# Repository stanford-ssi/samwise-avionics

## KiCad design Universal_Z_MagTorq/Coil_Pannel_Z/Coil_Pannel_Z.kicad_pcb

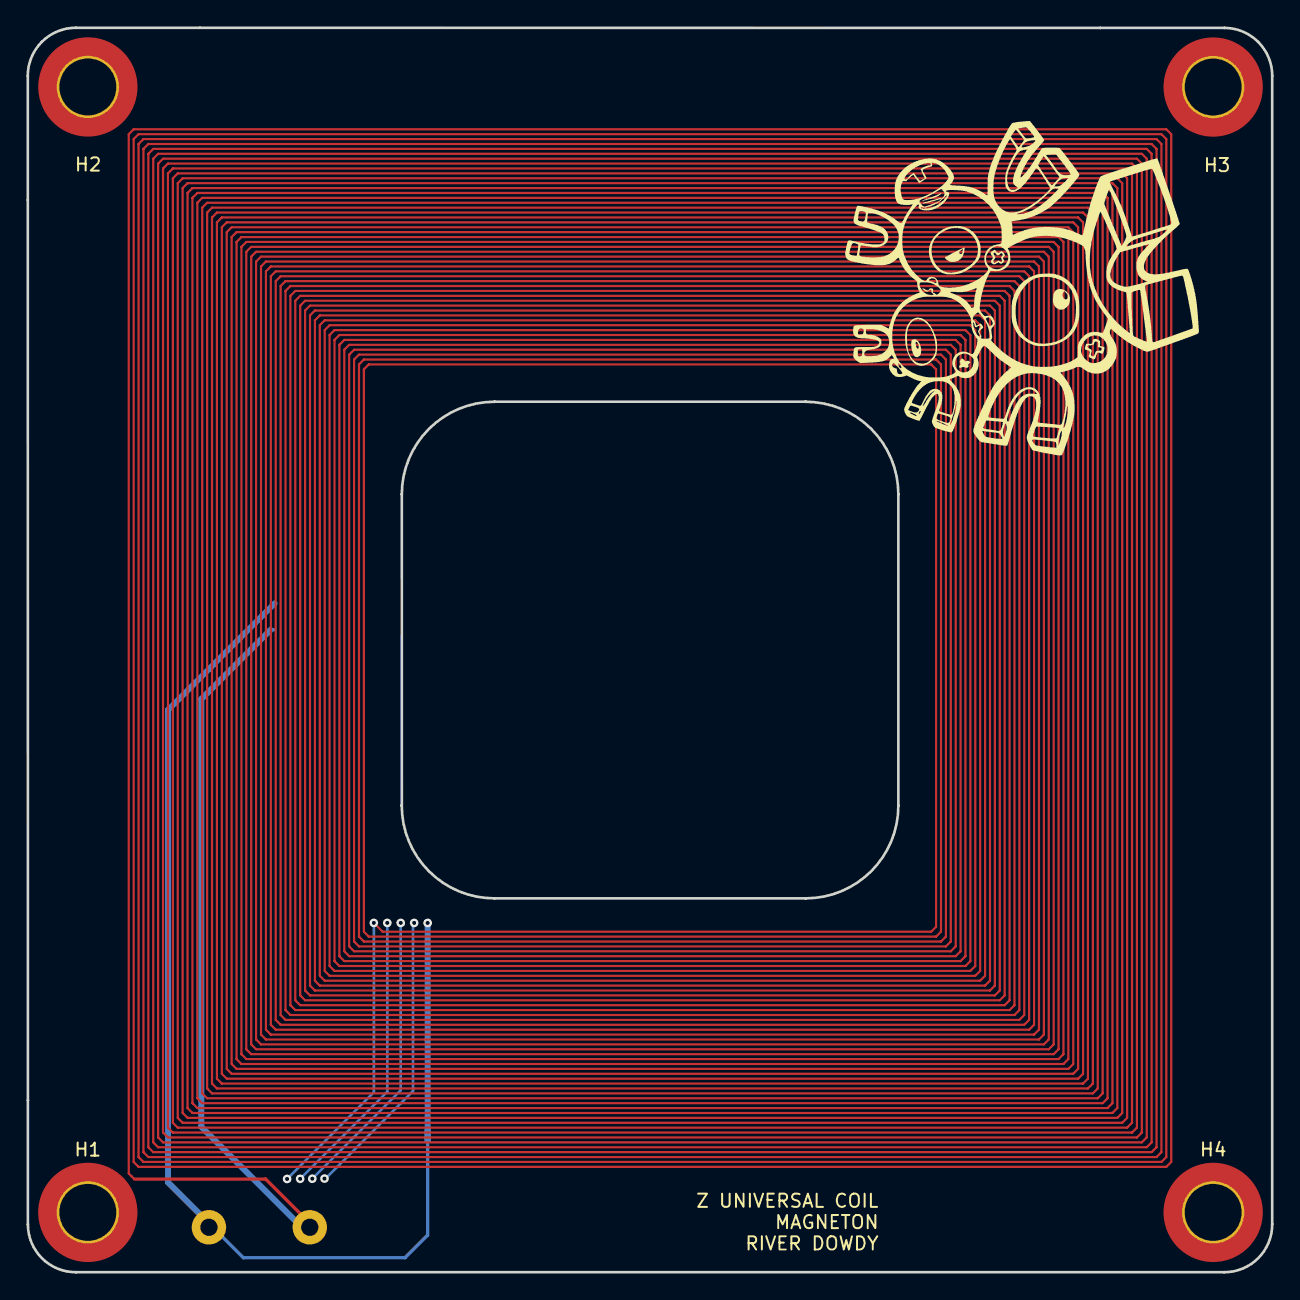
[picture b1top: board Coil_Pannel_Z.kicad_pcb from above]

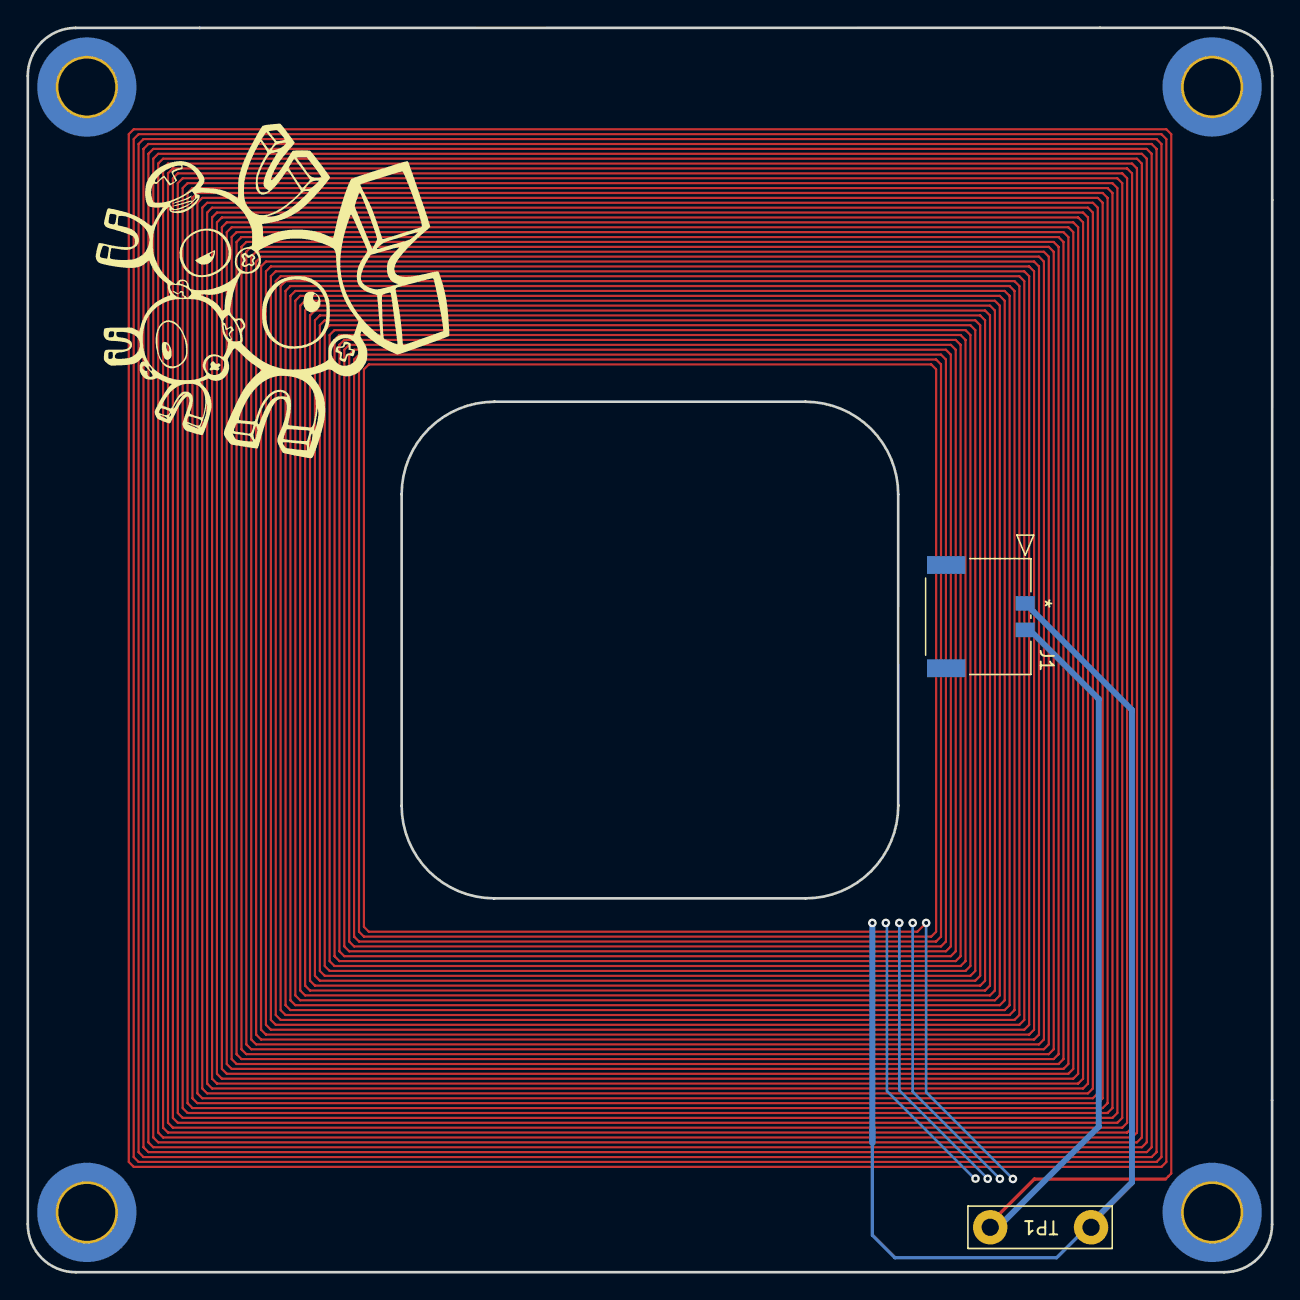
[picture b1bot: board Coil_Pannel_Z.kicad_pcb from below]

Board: 6 copper layers, 94.0 x 94.0 mm, 7 parts (3 on the bottom side), 2 nets.

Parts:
H1, H2, H3, H4: MountingHole_4.3mm_M4_DIN965_Pad_TopBottom
J1: 2053380002; Molex_205338-0002
NT1: NetTie_2; NetTie-2_SMD_Pad0.5mm
TP1: Start/End of Coil Series; TestPointConnection

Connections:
COIL_1: J1.1, NT1.1, TP1.1
COIL_2: J1.2, NT1.2, TP1.2

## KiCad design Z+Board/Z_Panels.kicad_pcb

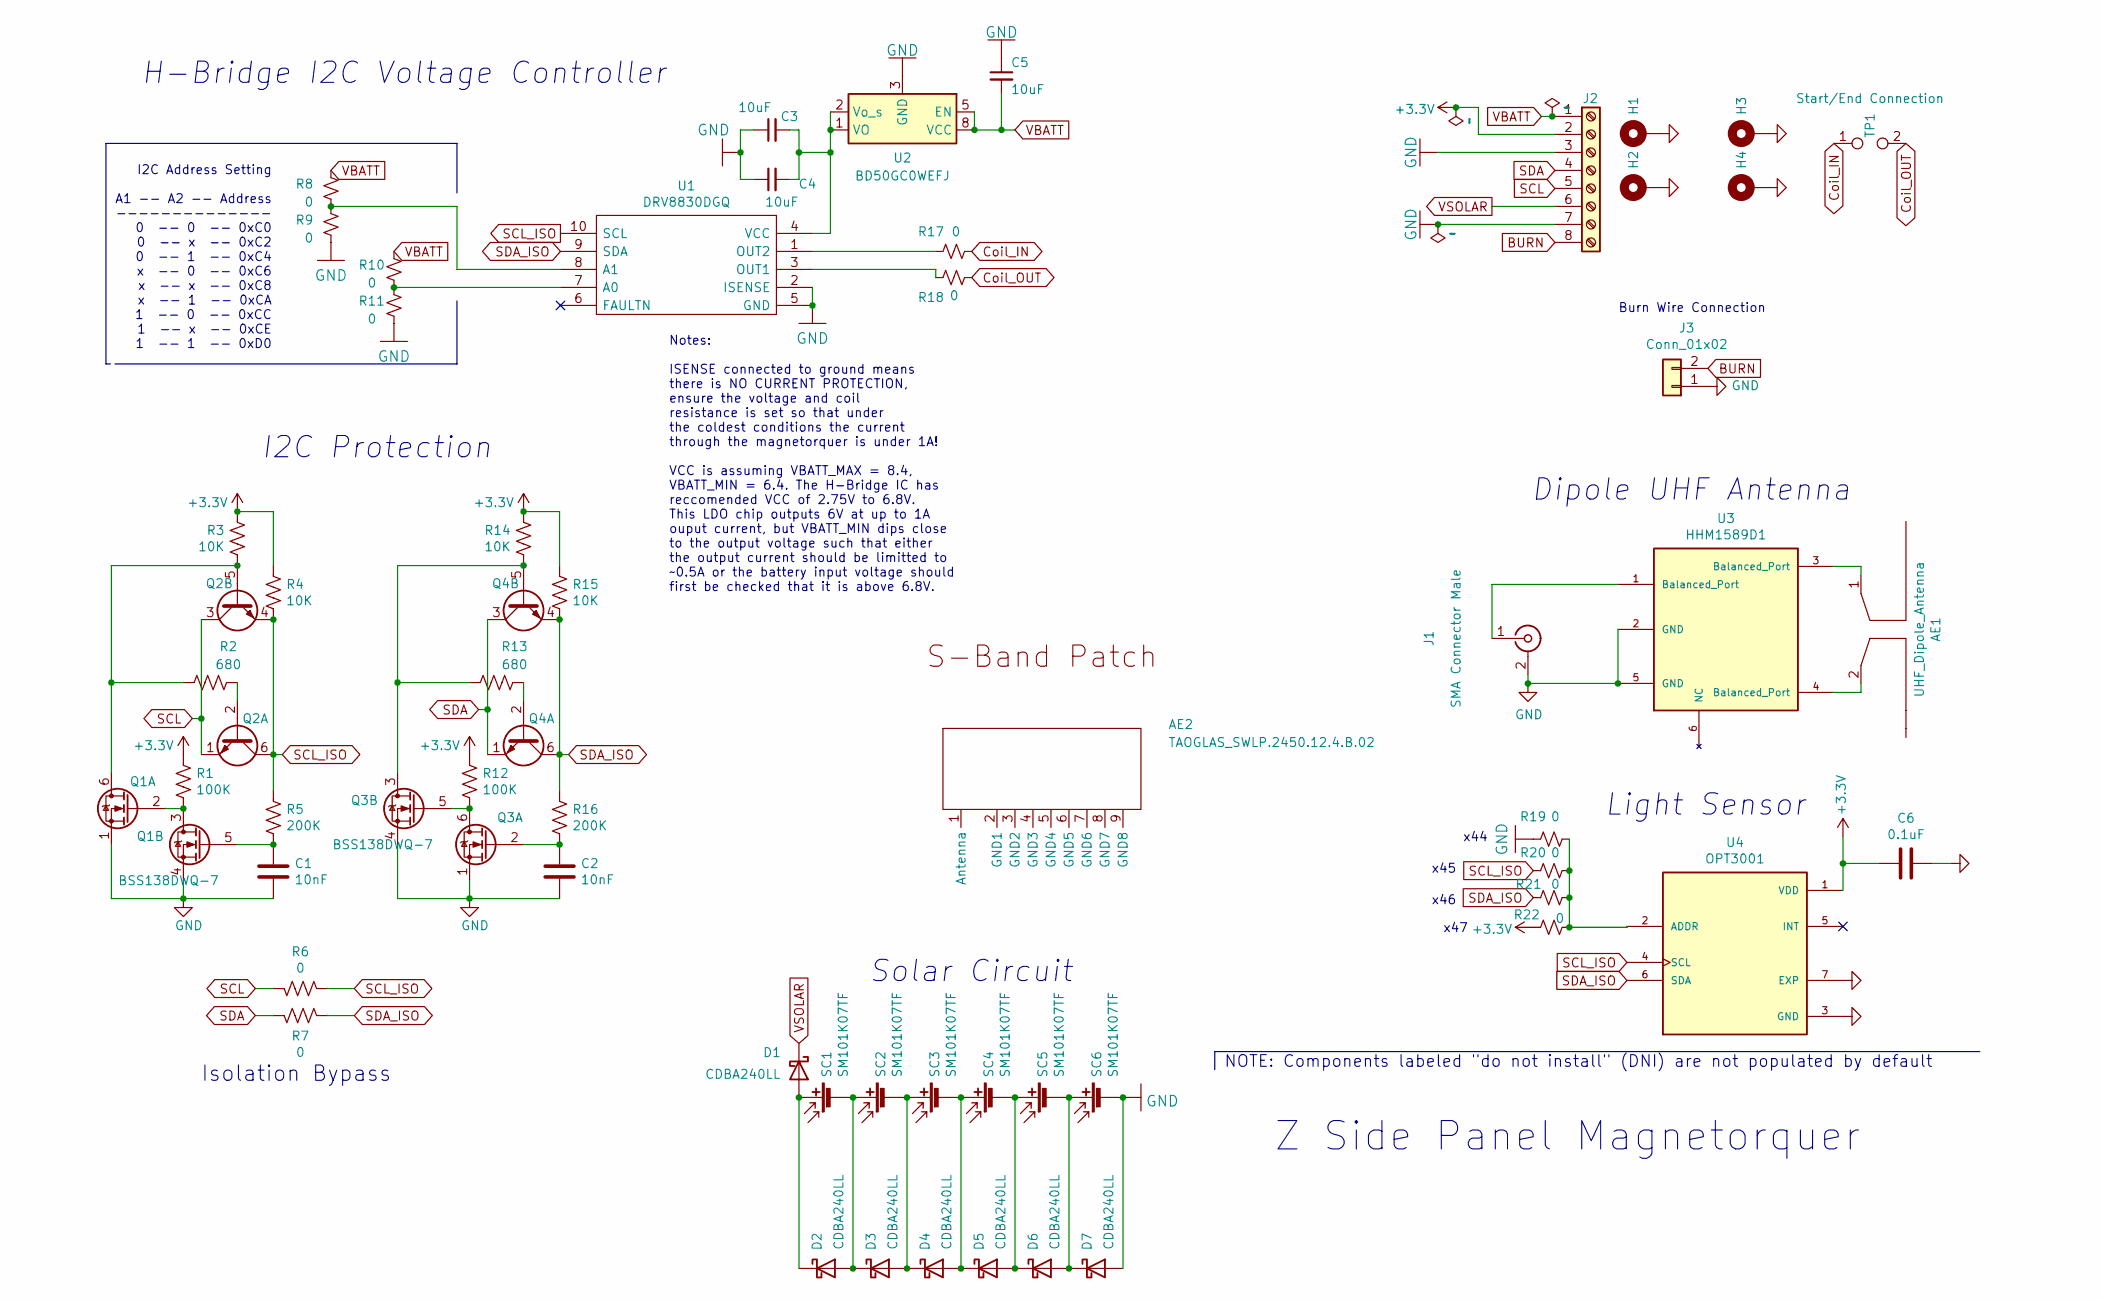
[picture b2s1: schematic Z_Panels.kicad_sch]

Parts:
AE1: UHF_Dipole_Antenna; UHF_Dipole_Antenna_Mount
AE2: TAOGLAS_SWLP.2450.12.4.B.02; S-Band Patch
C1, C2: 10nF; C_0603_1608Metric
C3, C4, C5: 10uF; C_1206_3216Metric
C6: 0.1uF; C_0603_1608Metric
D1, D2, D3, D4, D5, D6, D7: CDBA240LL; DO-214AC
H1, H2, H3, H4: MountingHole_2.2mm_M2_DIN965_Pad_TopBottom
J1: SMA Connector Male; SMA_Amphenol_901-144_Vertical
J2: Screw_Terminal_01x08; PinHeader_1x08_P2.54mm_Vertical
J3: Conn_01x02; Burn_Wire_Connection
Q1, Q3: BSS138DWQ-7; Manufacturer_Part_Number BSS138DWQ-7; Mouser Part Number 621-BSS138DWQ-7
Q2, Q4: MBT2222ADW1T1; SOT-363_SC-70-6
R1, R12: 100K; R_0603_1608Metric
R2, R13: 680; R_0603_1608Metric
R3, R4, R14, R15: 10K; R_0603_1608Metric
R5, R16: 200K; R_0603_1608Metric
R6, R7, R8, R9, R10, R11, R17, R18, R19, R20, R21, R22: 0; R_0603_1608Metric
SC1, SC2, SC3, SC4, SC5, SC6: SM101K07TF
TP1: Start/End Connection; TestPointConnection
U1: DRV8830DGQ; Manufacturer_Part_Number DRV8830DGQR; Mouser Part Number 595-DRV8830DGQR
U2: BD50GC0WEFJ; HTSOP-8-1EP_3.9x4.9mm_P1.27mm_EP2.4x3.2mm
U3: HHM1589D1
U4: OPT3001

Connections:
+3V3: C6.1, J2.2, R1.2, R3.1, R4.2, R12.2, R14.1, R15.2, R22.1, U4.1 (VDD)
BURN: J2.8, J3.2
Coil_IN: R17.2, TP1.1
Coil_OUT: R18.2, TP1.2
unnamed: AE1.1, U3.3 (Balanced_Port)
unnamed: AE1.2, U3.4 (Balanced_Port)
unnamed: D1.2 (A), D2.1 (K), SC1.1 (+)
unnamed: D2.2 (A), D3.1 (K), SC1.2 (-), SC2.1 (+)
unnamed: D3.2 (A), D4.1 (K), SC2.2 (-), SC3.1 (+)
unnamed: D4.2 (A), D5.1 (K), SC3.2 (-), SC4.1 (+)
unnamed: D5.2 (A), D6.1 (K), SC4.2 (-), SC5.1 (+)
unnamed: D6.2 (A), D7.1 (K), SC5.2 (-), SC6.1 (+)
unnamed: J1.1 (In), U3.1 (Balanced_Port)
unnamed: Q1.6 (D1), Q2.5 (B2), R2.1, R3.2
unnamed: Q1.2 (G2), Q1.3 (D2), R1.1
unnamed: C1.1, Q1.5 (G1), R5.1
unnamed: Q2.2 (B1), R2.2
unnamed: Q3.5 (G1), Q3.6 (D1), R12.1
unnamed: C2.1, Q3.2 (G2), R16.1
unnamed: Q3.3 (D2), Q4.5 (B2), R13.2, R14.2
unnamed: Q4.2 (B1), R13.1
unnamed: R10.2, R11.1, U1.7 (A0)
unnamed: R8.2, R9.1, U1.8 (A1)
unnamed: R18.1, U1.3 (OUT1)
unnamed: R17.1, U1.1 (OUT2)
unnamed: C3.2, C4.2, U1.4 (VCC), U2.1 (VO), U2.2 (Vo_s)
unnamed: R19.2, R20.2, R21.2, R22.2, U4.2 (ADDR)
SCL: J2.5, Q2.1 (E1), Q2.3 (C2), R6.1
SCL_ISO: Q2.4 (E2), Q2.6 (C1), R4.1, R5.2, R6.2, R20.1, U1.10 (SCL), U4.4 (SCL)
SDA: J2.4, Q4.1 (E1), Q4.3 (C2), R7.1
SDA_ISO: Q4.4 (E2), Q4.6 (C1), R7.2, R15.1, R16.2, R21.1, U1.9 (SDA), U4.6 (SDA)
VBATT: C5.2, J2.1, R8.1, R10.1, U2.5 (EN), U2.8 (VCC)
VSOLAR: D1.1 (K), J2.6

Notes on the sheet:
Notes: ISENSE connected to ground means there is NO CURRENT PROTECTION, ensure the voltage and coil resistance is set so that under the coldest conditions the current through the magnetorquer is under 1A! VCC is assuming VBATT_MAX = 8.4, VBATT_MIN = 6.4. The H-Bridge IC has reccomended VCC of 2.75V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
x47
Isolation Bypass
NOTE: Components labeled "do not install" (DNI) are not populated by default
Solar Circuit
x45
Z Side Panel Magnetorquer
Light Sensor
I2C Address Setting A1 -- A2 -- Address -------------- 0 -- 0 -- 0xC0 0 -- x -- 0xC2 0 -- 1 -- 0xC4 x -- 0 -- 0xC6 x -- x -- 0xC8 x -- 1 -- 0xCA 1 -- 0 -- 0xCC 1 -- x -- 0xCE 1 -- 1 -- 0xD0
H-Bridge I2C Voltage Controller
I2C Protection
Burn Wire Connection
Dipole UHF Antenna
x44
x46

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
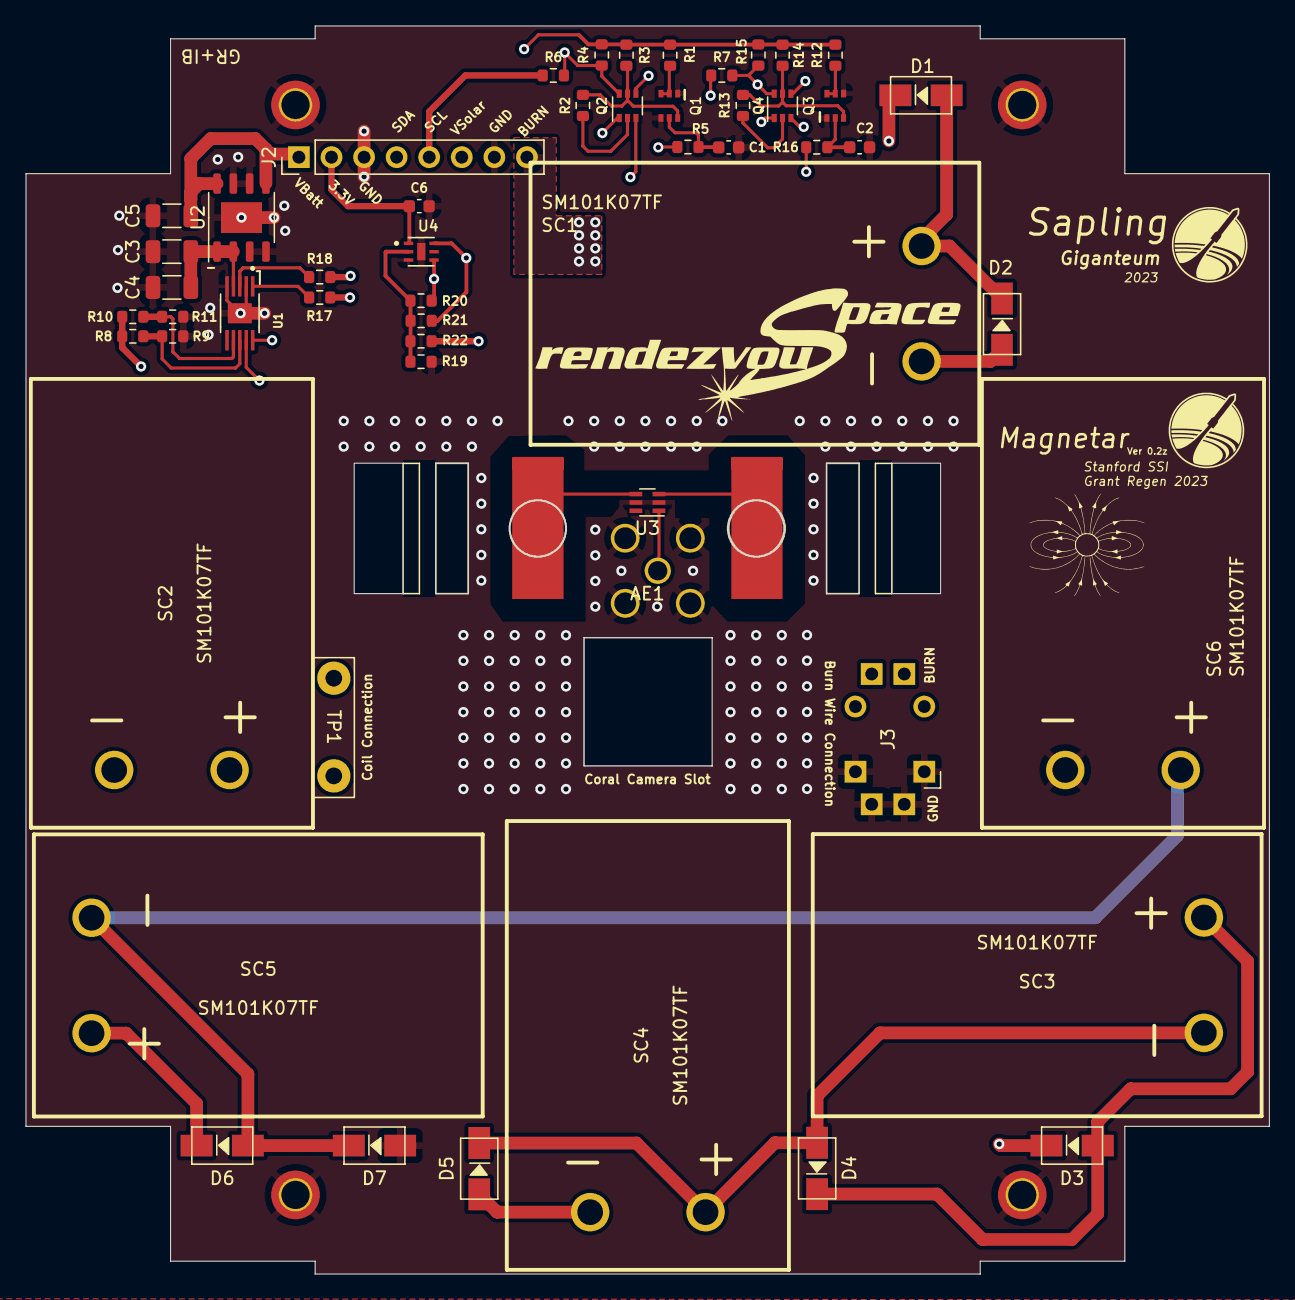
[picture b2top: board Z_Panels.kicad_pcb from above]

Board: 6 copper layers, 97.0 x 97.3 mm, 58 parts (1 on the bottom side), 34 nets.

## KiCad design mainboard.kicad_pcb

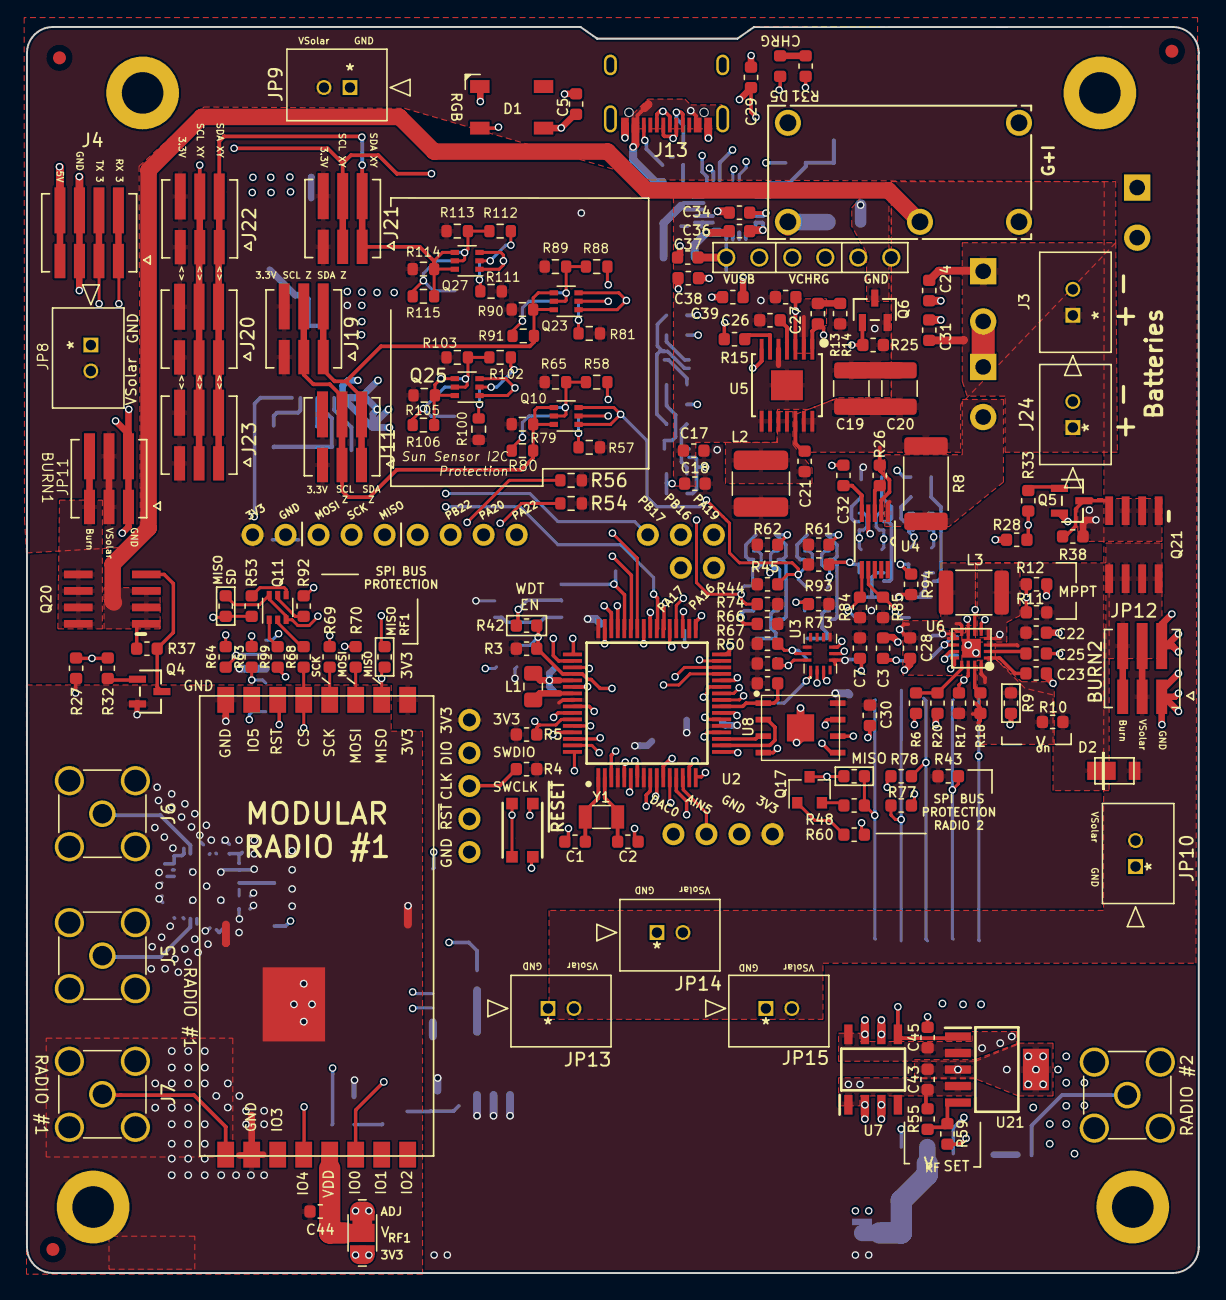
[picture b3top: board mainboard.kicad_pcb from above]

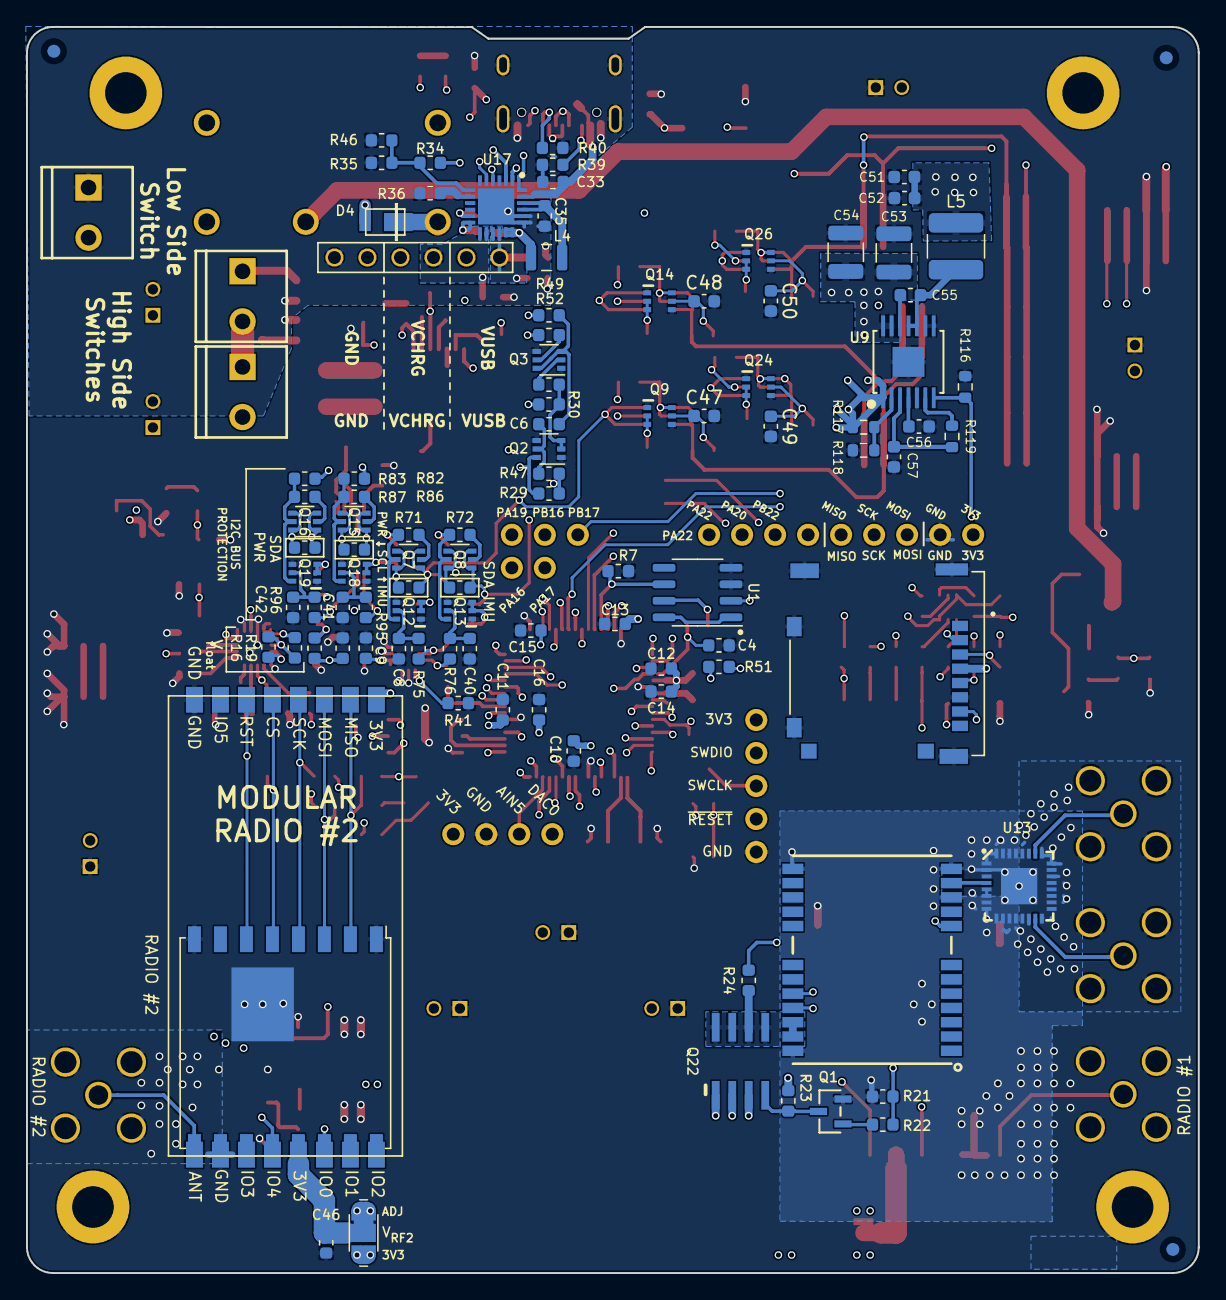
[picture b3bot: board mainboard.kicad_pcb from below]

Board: 4 copper layers, 90.2 x 95.9 mm, 275 parts (104 on the bottom side), 185 nets.

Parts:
C1, C2: 8pF; C_0603_1608Metric
C3, C5, C7, C9, C10, C11, C21, C24, C30, C45, C55: 0.1uF; C_0603_1608Metric
C4, C12, C13, C15, C27, C33, C57: 1uF; C_0603_1608Metric
C6, C14, C16, C22, C35, C39, C43, C44, C46: 10uF; C_0603_1608Metric
C8, C40, C41, C42, C47, C48, C49, C50: 10nF; C_0603_1608Metric
C17, C18, C28, C31, C37, C38, C51, C52: 22uF; C_0603_1608Metric
C19, C20, C53, C54: 100uF; C_1210_3225Metric
C23: 2.2uF; C_0603_1608Metric
C25: 22nF; C_0603_1608Metric
C26, C32, C56: 3.3nF; C_0603_1608Metric
C29, C34: 4.7uF; C_0603_1608Metric
C36: 47nF; C_0603_1608Metric
D1: WS2812B; LED_WS2812B_PLCC4_5.0x5.0mm_P3.2mm
D2, D4: DFLS130L; PWRDI-123
D5: GREEN LED; LED_0603_1608Metric
H1, H2, H3, H4: MountingHole_Pad; MountingHole_3.2mm_M3_DIN965_Pad
J1: 503182-1852; MOLEX_503182-1852
J2: Conn_01x05; PinHeader_1x05_P2.54mm_Vertical
J3, J24: MOLEX_Sherlock_2pos
J4: 874370443; MOLEX_874370443
J5, J6, J7: Amphenol_901-144; SMA_901-144-horizontal
J8: Conn_01x09; PinHeader_1x09_P2.54mm_Vertical
J9: Conn_01x03; PinHeader_1x03_P2.54mm_Vertical
J10: Conn_01x04; PinHeader_1x04_P2.54mm_Vertical
J11, J19, J20, J21, J22, J23: 874370343; MOLEX_874370343
J12: Amphenol_901-144; SMA_Amphenol_901-144_Vertical
J13: USB_C_pycubed; USB_C_Receptacle_XKB_U262-161N-4BVC11
J14: Conn_01x06; PinHeader_1x06_P2.54mm_Vertical
J15: Conn_01x02; PinHeader_CUSTOM3
J16, J17, J18: 1985807; SCREWTERMINAL-3.5MM-2_LOCK
JP6, JP7: Jumper_3_Bridged12; SolderJumper-3_P1.3mm_Bridged12_RoundedPad1.0x1.5mm
JP8, JP9, JP10, JP13, JP14, JP15: MOLEX_Sherlock_2pos
JP11, JP12: 874370343; MOLEX_874370343
L1: 10uH; L_0805_2012Metric_Pad1.15x1.40mm_HandSolder
L2: 3.3uH; L_2141
L3: 33uH; L_1812_4532Metric
L4: 1uH; L_2510
L5: 4.7uH; L_2141
Q1, Q4, Q5: IRLML2803; SOT-23
Q2, Q3, Q7, Q8, Q10, Q15, Q16, Q23, Q25, Q27: MBT2222ADW1T1; SOT-363_SC-70-6
Q6: MMBT2222AT; SOT-23
Q9, Q12, Q13, Q14, Q18, Q19, Q24, Q26: BSS138DWQ-7
Q11: MMDT2907; SOT-363_SC-70-6
Q17: MMBT2907; SOT-23
Q20, Q21, Q22: NDS8434
R1: 316K; R_0603_1608Metric
R2: 110K; R_0603_1608Metric
R3, R4, R21, R24, R31, R44, R45, R46, R52, R55, R61, R62, R65, R66, R67, R79, R82, R83, R84, R85, R89, R90, R103, R105, R113, R114: 10K; R_0603_1608Metric
R5, R7, R25, R27, R28, R41, R42, R43, R50, R51: 10k; R_0603_1608Metric
R6, R32, R33, R60, R92: 4.7k; R_0603_1608Metric
R8: 0.1; R_2512_6332Metric
R9: 107K; R_0603_1608Metric
R10, R48, R53, R97, R98, R99, R101, R104, R107, R108, R109: 0; R_0603_1608Metric
R11: 787K; R_0603_1608Metric
R12, R117: 121K; R_0603_1608Metric
R13, R29: 73.2K; R_0603_1608Metric
R14, R118: 22.1K; R_0603_1608Metric
R15, R30, R49, R57, R73, R74, R81, R93, R94, R100, R111, R119: 100K; R_0603_1608Metric
R16: 845K; R_0603_1608Metric
R17, R18, R37, R38: 100k; R_0603_1608Metric
R19: 2.1M; R_0603_1608Metric
R20: 3.01K; R_0603_1608Metric
R22, R54, R56, R68: 4.7K; R_0603_1608Metric
R23, R59: 3.3K; R_0603_1608Metric
R26, R63, R64, R69, R70, R77, R78: 1K; R_0603_1608Metric
R34: 5.23K; R_0603_1608Metric
R35: 30.1K; R_0603_1608Metric
R36: 3.16K; R_0603_1608Metric
R39, R40: 5.1k; R_0603_1608Metric
R47, R75, R76, R80, R91, R95, R96, R106, R115: 200K; R_0603_1608Metric
R58, R71, R72, R86, R87, R88, R102, R112: 680; R_0603_1608Metric
R110: 20K; R_0603_1608Metric
R116: 300K; R_0603_1608Metric
REF1B, REF1T, REF2B, REF2T, REF3B, REF3T: Fiducial_1mm_Mask2mm
SW1: KMR231NG LFS; BTN_KMR2_4.6X2.8
U1: MAX706RESA; SO-8_3.9x4.9mm_P1.27mm
U2: ATSAMD51J19A-AU; QFP50P1200X1200X120-64N
U3: BMX160
U4: ADM1176-1ARMZ-R7
U5, U9: TPS54226PWPRPWP14_2P31X2P46-L; PWP14_2P31X2P46-L
U6: LTC4121; QFN-16-PAD
U7: KF50BD-TR; SOIC127P600X175-8N
U8: MR25H40MDF; SON127P600X500X90-9N
U13: EP2W+; QFN32-5X5MM
U14: S1216V8; S1216_24PIN_PACKAGE
U15: RFM9xBreakout; HOPERF_RFM9XW_SMD
U16: PE014006; RELAY_PE014006
U17: BQ25883RGER; QFN50P400X400X100-25N-D
U21: TPS7A4501DCQT
U23, U24: RFM98PW; RFM95PW
Y1: 32.768kHz; Crystal_SMD_3215-2Pin_3.2x1.5mm

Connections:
3.3V: C5.1, C7.1, C9.2, C10.1, C11.1, C13.1, C15.1, C16.1, C17.2, C18.2, C30.1, D1.1, J1.4, J2.1, J8.1, J10.4, J11.3_1, J11.3_2, J19.3_1, J19.3_2, J20.3_1, J20.3_2, J21.3_1, J21.3_2, J22.3_1, J22.3_2, J23.3_1, J23.3_2, JP6.3, JP7.3, L2.2, Q22.1, Q22.2, Q22.3, R3.1, R4.1, R5.1, R13.2, R17.2, R18.2, R23.1, R43.1, R44.1, R45.1, R50.2, R51.2, R54.1, R56.1, R57.1, R61.1, R62.1, R65.1, R66.1, R67.1, R73.1, R74.1, R79.1, R81.1, R82.1, R83.1, R84.1, R85.1, R89.1, R90.1, R93.1, R94.1, R100.1, R103.1, R105.1, R111.1, R113.1, R114.1, U1.2, U2.4, U2.8, U2.21, U2.34, U2.48, U2.56, U3.5, U3.8, U3.12, U5.1, U8.8, U23.9, U24.9
5V: C51.2, C52.2, J4.4_1, J4.4_2, L5.2, R117.2, U9.1
/Avionics/BATTERY: C3.1, R1.2, R2.2, U2.15
/Avionics/XTAL1: C1.1, U2.1, Y1.1
/Avionics/XTAL2: C2.1, U2.2, Y1.2
/Burn Wires/VBURN1: JP11.3_1, JP11.3_2, Q20.5, Q20.6, Q20.7, Q20.8
/Burn Wires/VBURN2: JP12.3_1, JP12.3_2, Q21.5, Q21.6, Q21.7, Q21.8
/Burn Wires/VBURN_A_IN: Q20.1, Q20.2, Q20.3, Q21.1, Q21.2, Q21.3, R37.2, R38.2, U16.11
/Power/3V3_EN: Q2.6, R29.2, U5.7
/Power/REGN: C34.1, R31.2, U17.11
/Power/VCHRG_IN: C22.1, D2.C, R10.2, R11.2, U6.P$3
/Power/V_RF: C43.2, JP6.1, JP7.1, R55.1, U7.1, U21.4
/RF and GPS/RF1_ANT: J7.1, U23.1
/RF and GPS/RF2_ANT: J12.1, U15.9, U24.1
/RF and GPS/RF_IN: U13.4, U14.11
AIN5: J10.2, U2.14
BURN_RELAY_A: Q6.1, R25.1, U2.28
DAC0: J10.1, U2.3
ENAB_BURN1: R27.1, R32.2, U2.60
ENAB_BURN2: R28.1, R33.2, U2.32
ENAB_GPS: R21.1, R22.1, U2.62
ENAB_RF: U2.13, U7.5, U21.1
FLASH_CS: R50.1, U2.24, U8.1
FLASH_IO2: U2.19, U8.3
FLASH_IO3: U2.20, U8.7
FLASH_MISO: U2.18, U8.2
FLASH_MOSI: U2.17, U8.5
FLASH_SCK: U2.23, U8.6
GND: C1.2, C2.2, C3.2, C4.1, C5.2, C7.2, C8.2, C9.1, C10.2, C11.2, C12.1, C13.2, C14.2, C15.2, C16.2, C17.1, C18.1, C19.2, C20.2, C22.2, C23.2, C26.2, C27.2, C28.2, C30.2, C32.1, C40.2, C41.2, C42.2, C43.1, C44.1, C45.1, C46.1, C47.2, C48.2, C49.2, C50.2, C51.1, C52.1, C53.2, C54.2, C56.2, C57.2, D1.3, H1.1, H2.1, H3.1, H4.1, J1.6, J1.P1, J1.P2, J1.P3, J1.P4, J1.P5, J2.5, J4.3_1, J4.3_2, J5.2, J6.2, J7.2, J8.2, J10.3, J12.2, J14.5, J18.2, JP8.1, JP9.1, JP10.1, JP11.1_1, JP11.1_2, JP12.1_1, JP12.1_2, JP13.1, JP14.1, JP15.1, Q1.2, Q2.1, Q2.4, Q3.1, Q3.4, Q4.2, Q5.2, Q6.2, Q9.1, Q9.4, Q12.1, Q12.4, Q13.1, Q13.4, Q14.1, Q14.4, Q18.1, Q18.4, Q19.1, Q19.4, Q24.1, Q24.4, Q26.1, Q26.4, R2.1, R7.1, R9.2, R12.1, R14.1, R20.1, R21.2, R25.2, R27.2, R28.2, R41.2, R59.2, R116.1, R118.1, SW1.B, SW1.B', U1.3, U1.4, U2.7, U2.22, U2.33, U2.47, U2.54, U3.2, U3.3, U3.6, U3.7, U4.4, U5.5, U5.8, U5.9, U5.15, U6.P$5, U6.P$7, U6.P$12, U6.P$17, U7.2, U7.3, U7.6, U7.7, U8.4, U8.9, U9.5, U9.8, U9.9, U9.15, U13.1, U13.2, U13.3, U13.5, U13.6, U13.7, U13.8, U13.9, U13.10, U13.11, U13.12, U13.13, U13.14, U13.16, U13.17, U13.18, U13.19, U13.20, U13.21, U13.22, U13.23, U13.24, U13.25, U13.27, U13.28, U13.29, U13.30, U13.31, U13.32, U13.EP, U14.10, U14.12, U14.13, U14.24, U15.1, U15.8, U15.10, U16.12, U21.3, U21.6, U23.2, U23.16, U23.17, U24.2, U24.16, U24.17
GNDREF: C24.2, C29.2, C31.2, C33.1, C34.2, C35.1, C37.1, C38.1, C39.1, J3.2, J13.A1, J13.A12, J13.S1, J14.6, J18.1, J24.2, R35.1, R36.1, R39.1, R40.1, R46.1, U17.19, U17.20, U17.25
GPS_PWR_IN: Q22.5, Q22.6, Q22.7, Q22.8, R24.2, U14.22, U14.23
L1_PROG: R6.1, R20.2, U6.P$13
MISO: J8.5, Q11.3, Q11.6, Q17.3, R101.2, R104.2, R107.2, U2.31
MISO_RF1: R99.2, R101.1, U23.10
MISO_RF2: R48.2, R107.1, U15.2, U24.10
MISO_SD: J1.7, R53.2, R104.1
MOSI: J8.3, R64.2, R70.1, R77.2, U2.29
MOSI_RF1: R70.2, U23.11
MOSI_RF2: R77.1, U15.3, U24.11
MOSI_SD: J1.3, R64.1
unnamed: C6.1, Q3.3, Q3.6, R49.2
unnamed: C6.2, Q2.5, R47.2
unnamed: C8.1, Q12.5, R75.2
unnamed: C12.2, C14.1, L1.1, U2.53
unnamed: C21.1, L2.1, U5.10, U5.11
unnamed: C21.2, U5.12
unnamed: C23.1, U6.P$1
unnamed: C25.1, U6.P$2
unnamed: C25.2, L3.2, U6.P$4
unnamed: C26.1, U5.4
unnamed: C27.1, R15.2, U5.3
unnamed: C32.2, U4.5
unnamed: C35.2, L4.1, U17.21, U17.22
unnamed: C36.1, L4.2, U17.17, U17.18
unnamed: C36.2, U17.12
unnamed: C37.2, C38.2, J14.1, U17.15, U17.16
unnamed: C39.2, J14.3, U17.13, U17.14
unnamed: C40.1, Q13.5, R76.2
unnamed: C41.1, Q18.5, R95.2
unnamed: C42.1, Q19.5, R96.2
unnamed: C47.1, Q9.5, R80.2
unnamed: C48.1, Q14.5, R91.2
unnamed: C49.1, Q24.5, R106.2
unnamed: C50.1, Q26.5, R115.2
unnamed: C55.1, L5.1, U9.10, U9.11
unnamed: C55.2, U9.12
unnamed: C56.1, U9.4
unnamed: C57.1, R119.2, U9.3
unnamed: D1.4, U2.42
unnamed: D4.A, Q6.3, U16.5
unnamed: D5.2, R31.1
unnamed: J5.1, U13.15
unnamed: J6.1, U13.26
unnamed: J16.2, J17.1
unnamed: L1.2, U2.55
unnamed: L3.1, U6.P$8
unnamed: Q1.1, R22.2
unnamed: Q1.3, Q22.4, R23.2
unnamed: Q2.2, Q2.3, R30.2, R110.2
unnamed: Q3.2, R110.1
unnamed: Q3.5, R52.1
unnamed: Q4.1, R32.1
unnamed: Q5.1, R33.1
unnamed: Q7.2, R71.1
unnamed: Q8.2, R72.1
unnamed: Q9.2, Q9.3, R57.2
unnamed: Q10.2, R58.1
unnamed: Q9.6, Q10.5, R58.2, R65.2
unnamed: Q11.1, R99.1
unnamed: Q11.2, R68.1
unnamed: Q11.4, R53.1
unnamed: Q11.5, R92.1
unnamed: Q12.2, Q12.3, R73.2
unnamed: Q7.5, Q12.6, R61.2, R71.2
unnamed: Q13.2, Q13.3, R74.2
unnamed: Q8.5, Q13.6, R62.2, R72.2
unnamed: Q14.2, Q14.3, R81.2
unnamed: Q14.6, Q23.5, R88.2, R89.2
unnamed: Q15.2, R86.1
unnamed: Q15.5, Q18.6, R82.2, R86.2
unnamed: Q16.2, R87.1
unnamed: Q16.5, Q19.6, R83.2, R87.2
unnamed: Q17.1, R60.1
unnamed: Q17.2, R48.1
unnamed: Q18.2, Q18.3, R93.2
unnamed: Q19.2, Q19.3, R94.2
unnamed: Q4.3, Q20.4, R37.1
unnamed: Q5.3, Q21.4, R38.1
unnamed: Q23.2, R88.1
unnamed: Q24.2, Q24.3, R100.2
unnamed: Q24.6, Q25.5, R102.2, R103.2
unnamed: Q25.2, R102.1
unnamed: Q26.2, Q26.3, R111.2
unnamed: Q26.6, Q27.5, R112.2, R113.2
unnamed: Q27.2, R112.1
unnamed: R6.2, U2.16
unnamed: R9.1, R10.1, U6.P$16
unnamed: R11.1, R12.2, U6.P$6
unnamed: R13.1, R14.2, U5.2
unnamed: R15.1, U5.6
unnamed: R16.1, U6.P$11
unnamed: R16.2, R19.2, U6.P$10
unnamed: R18.1, U6.P$15
unnamed: R24.1, U14.8
unnamed: R26.2, U4.3
unnamed: R36.2, U17.8
unnamed: R41.1, U3.1
unnamed: R42.2, U1.7
unnamed: R55.2, R59.1, U21.5
unnamed: R117.1, R118.2, U9.2
unnamed: R119.1, U9.6
unnamed: U1.1, U1.8
PA16: J15.2, Q27.1, Q27.3, R56.2, U2.35
PA17: J15.1, Q25.1, Q25.3, R54.2, U2.36
PA19: J9.3, U2.38
PA20: J8.8, U2.41
PA22: J8.9, U2.43
PB16: J4.2_1, J4.2_2, J9.2, U2.39
PB17: J4.1_1, J4.1_2, J9.1, U2.40
PB22: J8.7, U2.49
PB23: R116.2, U2.50, U9.7
RF1_CS: R5.2, R68.2, U2.59, U23.13
RF1_IO0: U2.6, U23.6
RF1_IO4: U2.5, U23.4
RF1_RST: U2.61, U23.14
RF2_CS: R43.2, R60.2, U2.12, U15.5, U24.13
RF2_IO0: U2.9, U15.14, U24.6
RF2_IO4: U2.10, U15.12, U24.4
RF2_RST: U2.27, U15.6, U24.14
RX: U2.64, U14.20
SCK: J8.4, R63.2, R69.2, R78.2, U2.30
SCK_RF1: R69.1, U23.12
SCK_RF2: R78.1, U15.4, U24.12
SCK_SD: J1.5, R63.1
SCL: Q7.1, Q7.3, Q10.1, Q10.3, Q15.1, Q15.3, R45.2, R97.2, R108.2, U2.26
SCL_IMU: Q7.4, Q7.6, R66.2, R75.1, R97.1, U3.13
SCL_PWR: Q15.4, Q15.6, R84.2, R95.1, R108.1, U4.6, U17.5
SCL_SS_XY: J20.2_1, J20.2_2, J21.2_1, J21.2_2, J22.2_1, J22.2_2, J23.2_1, J23.2_2, Q25.4, Q25.6, R105.2, R106.1
SCL_SS_Z: J11.2_1, J11.2_2, J19.2_1, J19.2_2, Q10.4, Q10.6, R79.2, R80.1
SDA: Q8.1, Q8.3, Q16.1, Q16.3, Q23.1, Q23.3, R44.2, R98.2, R109.2, U2.25
SDA_IMU: Q8.4, Q8.6, R67.2, R76.1, R98.1, U3.14
SDA_PWR: Q16.4, Q16.6, R85.2, R96.1, R109.1, U4.7, U17.4
SDA_SS_XY: J20.1_1, J20.1_2, J21.1_1, J21.1_2, J22.1_1, J22.1_2, J23.1_1, J23.1_2, Q27.4, Q27.6, R114.2, R115.1
SDA_SS_Z: J11.1_1, J11.1_2, J19.1_1, J19.1_2, Q23.4, Q23.6, R90.2, R91.1
SD_CS: J1.2, R51.1, R92.2, U2.51
STAT: D5.1, U17.2
SWCLK: J2.3, R4.2, U2.57
SWDIO: J2.2, U2.58
THM: R34.2, R35.2, R46.2, U17.7
TX: U2.63, U14.21
USB_CC1: J13.A5, R40.2
USB_CC2: J13.B5, R39.2
USB_D+: J13.A6, J13.B6, U2.46, U17.24
USB_D-: J13.A7, J13.B7, U2.45, U17.1
VBATT: C19.1, C20.1, C28.1, C45.2, C53.1, C54.1, D4.C, J14.2, R1.1, R8.1, R19.1, R26.1, R29.1, R30.1, R47.1, R49.1, U4.2, U5.13, U5.14, U6.P$9, U7.8, U9.13, U9.14, U16.1, U16.14, U21.2
VBATT_SENSE: J17.2, R8.2, U4.1
VBUS_IN: C29.1, C33.2, J13.A4, J13.A9, R34.1, U17.23
VBUS_RESET: R52.2, U2.37
VCC_RF1: C44.2, JP6.2, U23.5
VCC_RF2: C46.2, JP7.2, U15.13, U24.5
VCHRG: C24.1, C31.1, J3.1, J14.4, J16.1, J24.1
VSOLAR: D2.A, JP8.2, JP9.2, JP10.2, JP11.2_1, JP11.2_2, JP12.2_1, JP12.2_2, JP13.2, JP14.2, JP15.2
WDT_WDI: R7.2, U1.6, U2.44
~CHRG: R17.1, U2.11, U6.P$14
~RESET: C4.2, J2.4, R3.2, R42.1, SW1.A, SW1.A', U2.52

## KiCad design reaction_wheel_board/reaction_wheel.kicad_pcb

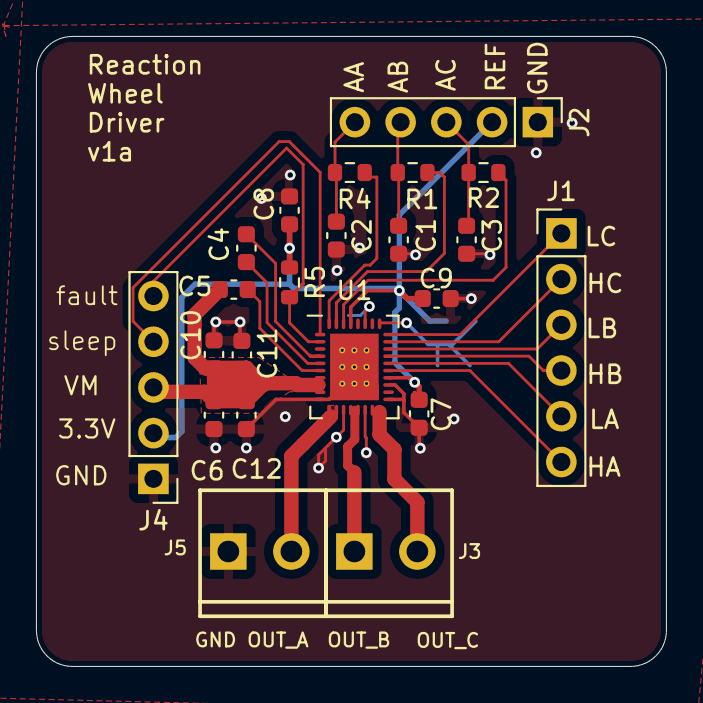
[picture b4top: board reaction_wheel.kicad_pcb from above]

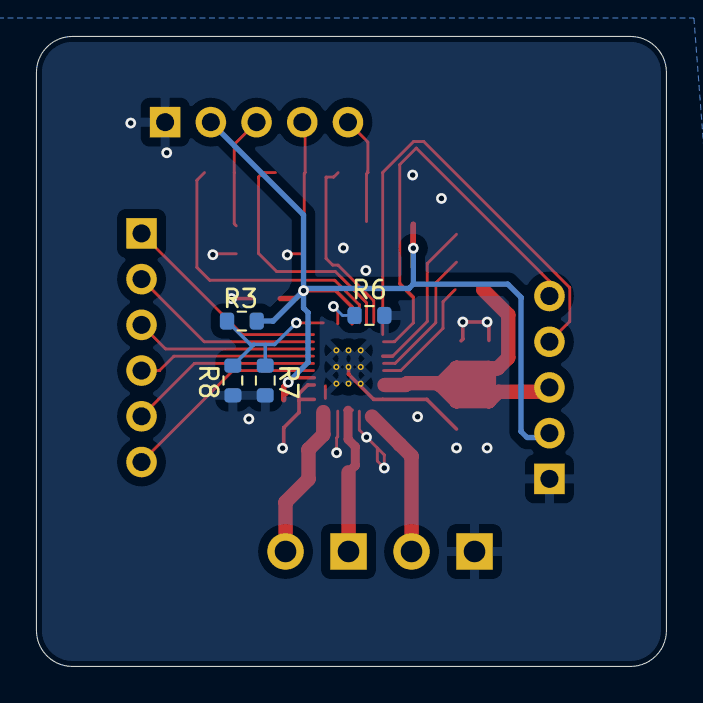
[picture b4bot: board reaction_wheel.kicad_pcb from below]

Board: 2 copper layers, 35.0 x 35.0 mm, 26 parts (4 on the bottom side), 25 nets.

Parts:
C1, C2, C3: 22pF; C_0603_1608Metric
C4: 47nF; C_0603_1608Metric
C5, C6, C8, C9, C11: 0.1μF; C_0603_1608Metric
C7: 4.7μF; C_0603_1608Metric
C10, C12: 10μF; C_0603_1608Metric
J1: PWM Pins; PinHeader_1x06_P2.54mm_Vertical
J2: Conn_01x05; PinHeader_1x05_P2.54mm_Vertical
J3, J5: Screw_Terminal_01x02; 1985807
J4: Power Pins; PinHeader_1x05_P2.54mm_Vertical
R1, R2, R4: 330; R_0603_1608Metric
R3, R7: 0R; R_0603_1608Metric
R5: 5.1kΩ; R_0603_1608Metric
R6, R8: 47k; R_0603_1608Metric
U1: DRV8317HREER; QFN-36_EP_4.6x5.4_Pitch0.4mm

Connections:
+3.3V: C7.1, C8.2, C9.2, J2.2, J4.2, R3.2, R5.1, U1.22 (AVDD), U1.33 (CSAREF)
+12V: C5.1, C6.2, C10.2, C11.2, C12.2, J4.3, U1.7 (VIN_AVDD), U1.8 (VM), U1.9 (VM)
/ADC_A: C2.1, J2.5, R4.2
/ADC_B: C1.1, J2.4, R1.2
/ADC_C: C3.1, J2.3, R2.2
/OUT_A: J5.2, U1.11 (OUTA), U1.12 (OUTA)
/OUT_B: J3.1, U1.14 (OUTB), U1.15 (OUTB)
/OUT_C: J3.2, U1.17 (OUTC), U1.18 (OUTC)
/PWM_H_A: J1.6, U1.23 (INHA)
/PWM_H_B: J1.4, U1.25 (INHB)
/PWM_H_C: J1.2, U1.27 (INHC)
/PWM_L_A: J1.5, U1.24 (INLA)
/PWM_L_B: J1.3, U1.26 (INLB)
/PWM_L_C: J1.1, U1.28 (INLC)
/fault: J4.5, R5.2, U1.2 (NFAULT)
/sleep: J4.4, U1.1 (NSLEEP)
GND: C1.2, C2.2, C3.2, C6.1, C7.2, C8.1, C9.1, C10.1, C11.1, C12.1, J2.1, J4.1, J5.1, R6.2, R7.1, R8.1, U1.10 (PGND), U1.13 (PGND), U1.16 (PGND), U1.19 (PGND), U1.21 (AGND), U1.37 (EPAD)
unnamed: C5.2, U1.6 (CP)
unnamed: C4.2, U1.5 (CPH)
unnamed: C4.1, U1.4 (CPL)
unnamed: R3.1, R7.2, R8.2, U1.29 (GAIN)
unnamed: R6.1, U1.31 (MODE)
unnamed: R4.1, U1.36 (SOA)
unnamed: R1.1, U1.35 (SOB)
unnamed: R2.1, U1.34 (SOC)

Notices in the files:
parts and their libraries:
Copyright 2021 Accelerated Designs. All rights reserved.
Copyright 2016 Accelerated Designs. All rights reserved.
